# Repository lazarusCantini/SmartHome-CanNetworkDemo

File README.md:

# SmartHome-CanNetworkDemo
Dieses Repository beinhaltet alle Dateien die Nötig sind, um das CAN NetzwerkDemo-Board aufzubauen.
## Aufbau
### Schema

### Foto

### Pinbelegung für alle drei Arduinos gleich
CAN-BUS Modul | Arduino | ATMEGA328P
--------------|---------|-----------
INT (Invertiert)|2|PD2
SCK SPI CLK|13|PB5
SI MOSI|11|PB3
SO MISO|12|PB4
CS Chip Select|10|PB2
GND|GND|GND
VCC1 Versorgung|5V|\-
VCC Spg. Logikpegel|5V|\-

### Zuordnung ATMEGA328P Pins <-> Arduino
ATMEGA328P | Arduino
-----------|--------
PB0|8
PB1|9
PB2|10
PB3|11
PB4|12
PB5|13
PC0|A0
PC1|A1
PC2|A2
PC3|A3
PC4|A4
PC5|A5
PD0|0
PD1|1
PD2|2
PD3|3
PD4|4
PD5|5
PD6|6
PD7|7

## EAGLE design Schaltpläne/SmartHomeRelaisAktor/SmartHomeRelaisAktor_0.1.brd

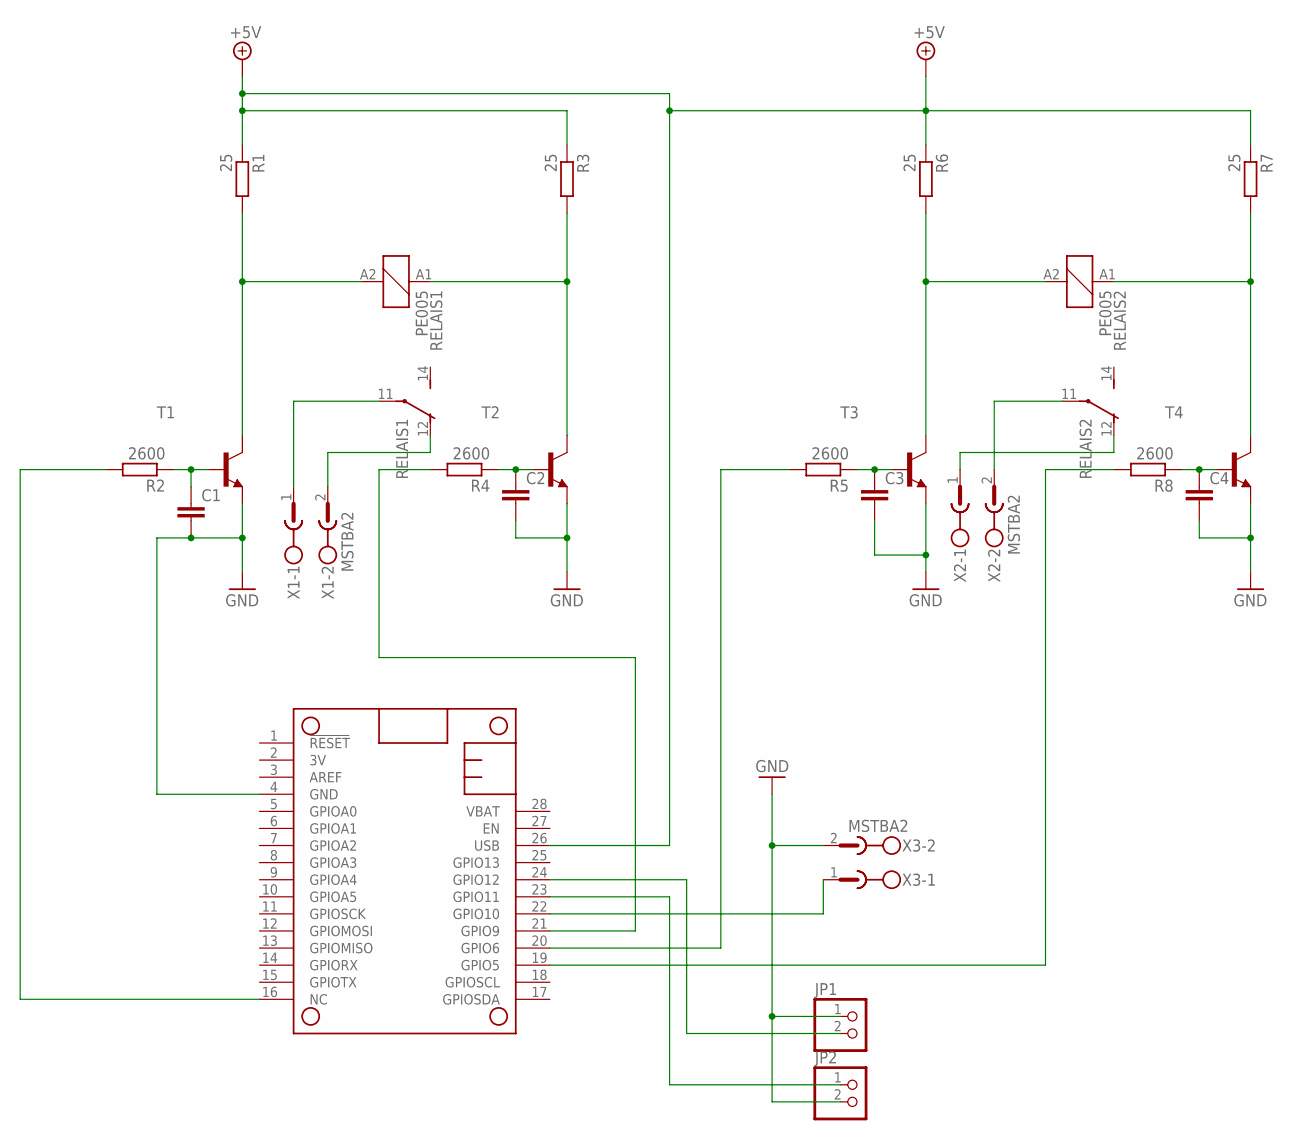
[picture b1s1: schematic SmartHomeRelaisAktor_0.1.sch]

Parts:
C1, C2, C3, C4: C-EUC0805; C0805
JP1, JP2: PINHD-1X2; 1X02
MS1: FEATHERWING
R1, R3, R6, R7: 25; R0805
R2, R4, R5, R8: 2600; R0805
RELAIS1, RELAIS2: PE005; PE
T1, T2, T3, T4: BC817-16-NPN-SOT23-BEC; SOT23-BEC
X1, X2, X3: MSTBA2

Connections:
GND: C1.2, C2.2, C3.2, C4.2, JP1.1, JP2.2, MS1.4 (GND), T1.E, T2.E, T3.E, T4.E, X3.2
unnamed: R1.2, RELAIS1.A2 (2), T1.C
unnamed: R3.2, RELAIS1.A1 (1), T2.C
unnamed: C2.1, R4.1, T2.B
unnamed: C3.1, R5.1, T3.B
unnamed: C1.1, R2.1, T1.B
unnamed: R6.2, RELAIS2.A2 (2), T3.C
unnamed: R7.2, RELAIS2.A1 (1), T4.C
unnamed: C4.1, R8.1, T4.B
unnamed: MS1.16 (NC), R2.2
unnamed: MS1.21 (GPIO9), R4.2
unnamed: MS1.20 (GPIO6), R5.2
unnamed: MS1.22 (GPIO10), X3.1
unnamed: RELAIS2.11, X2.2
unnamed: RELAIS1.12 (O), X1.2
unnamed: RELAIS1.11, X1.1
unnamed: MS1.19 (GPIO5), R8.2
unnamed: RELAIS2.12 (O), X2.1
unnamed: JP1.2, MS1.24 (GPIO12)
unnamed: JP2.1, MS1.23 (GPIO11)
USB: MS1.26 (USB), R1.1, R3.1, R6.1, R7.1

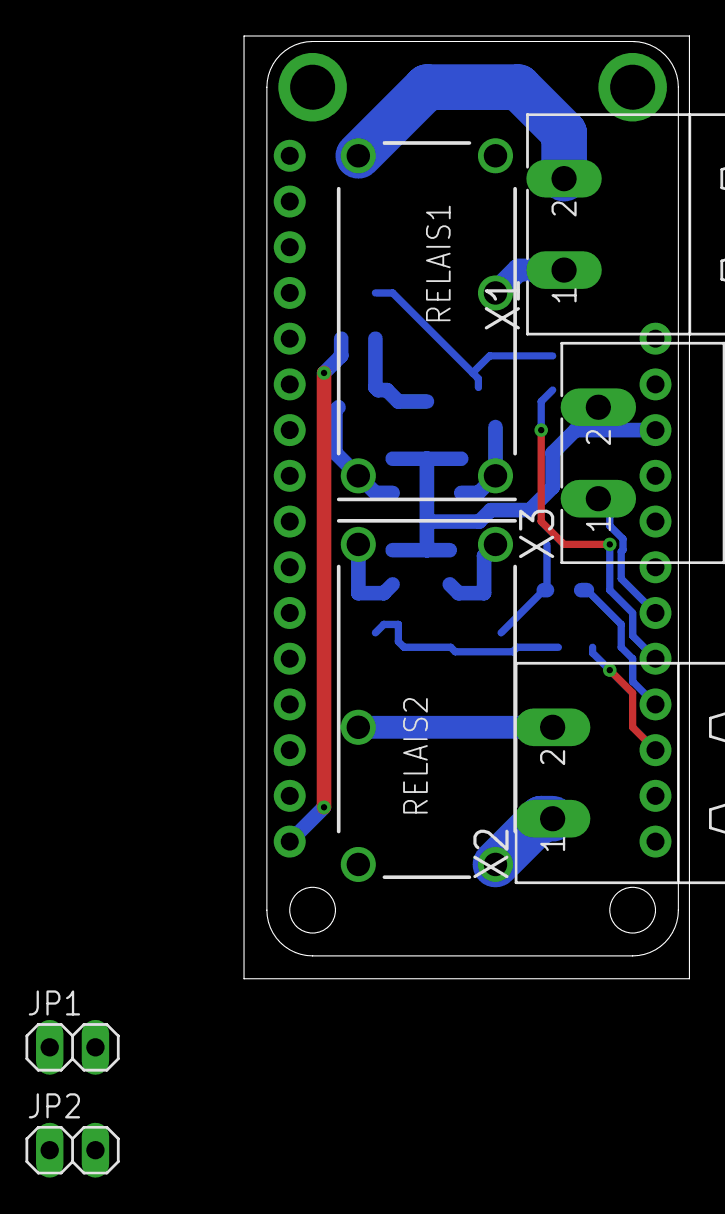
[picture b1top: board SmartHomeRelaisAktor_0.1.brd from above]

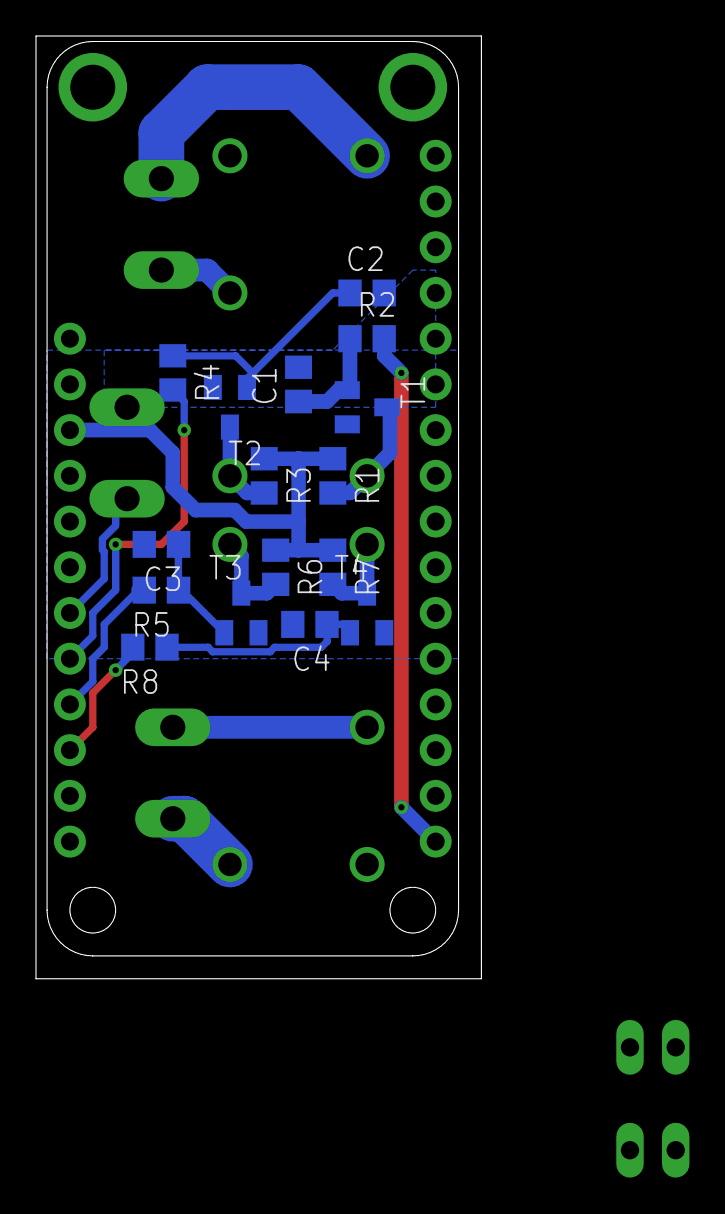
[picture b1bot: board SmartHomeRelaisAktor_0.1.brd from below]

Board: 2 copper layers, 24.7 x 52.4 mm, 24 parts (16 on the bottom side), 21 nets.

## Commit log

2019-03-28 Aufbau Schema gezeichnet
2019-03-29 Aufbau Schema Vervollständigt
2019-03-31 Quellcode für Node und HUB eingefügt
    Vom privaten Notebook aus dem AtmelStudio Ordner ins GitHub verschoben
2019-03-31 Ordner verschoben
2019-03-31 Kontrolliert: SetzeIDZusammen(uint8_t *CAN_Array)
    Die Funrktion wurde in C++ mit Codeblocks nachgeprüft und setzt das 8-Bit Array erwartungsmäß zusammen
2019-03-31 Arbeiten beendet
2019-04-02 Debugging ID Liste ausgabe wird noch korrigiert
2019-04-02 Batch Datei zum übertragen des Nodes vom Bürorechner aus erstellt
2019-04-03 Optimierung an Funktion void ID_Ausgeben(uint32_t ID) ausgeschaltet. Muss getestet werden, ob das eine Veränderung bringt
    __attribute__((optimize(0)))
2019-04-03 Create .gitignore
    Habe versucht alle Dateien auszunehmen, die sowieso bei jedem Kompiliervorgang neu erstellt werden, und unnötige "changed files" und History erzeugen
2019-04-03 void ID_Ausgeben(uint32_t ID) funktioniert endlich
2019-04-03 Versuche die automatisch generierten Dateien aus dem Projekt zu entfernen
2019-04-03 weitere automatisch generierten Dateien entfernt
2019-04-03 gitignore Test
2019-04-05 Pinout Arduino <-> ATMEGA328P hinzugefügt
2019-04-05 Pin Bibliothek hinzugefügt, und LED Pins definiert
2019-04-05 Revert "Pinout Arduino <-> ATMEGA328P hinzugefügt"
    This reverts commit 67fae2733ddc45ce7ad68df869293d14515be329.
2019-04-05 Revert "Revert "Pinout Arduino <-> ATMEGA328P hinzugefügt""
    This reverts commit 0b71fdb48e68ebb74e261073c404b3e81173cc3d.
2019-04-05 irgendwas ist schief gelaufen
2019-04-05 immer noch wiederherstellung
2019-04-05 imme rnoch
2019-04-05 Sensor Aktor Board wiederhergestellt
2019-04-05 Master funktioniert wieder
2019-04-05 Pin Bibliothek eingebunden und angefangen zu verwenden
2019-04-05 Angefangen mit dem remote schalten der LED
2019-04-08 Fast fertig mit Hardgecodetem Schalten einer LED. togglePin von ATMEGA328.cpp scheint nicht zu funktionieren
2019-04-08 Led wird per CAN Nachricht getoggelt
    Projekt To-Do Schalten eines Aktors über das CAN Netzwerk, getriggert Hardgecodet vom HUB ist abgeschlossen
2019-04-09 Beispiel CAN Arduino Script hinzugefügt
2019-04-10 Zweiten Node für Taster hinzugefügt
2019-04-10 Allen Text aus der Sketch.cpp von Node 1 in die Datei Sketch.cpp von Node2 kopiert
2019-04-10 Bild für Wiki eingefügt
2019-04-10 Bilder fürs Wiki hinzugefügt
2019-04-10 Bild für WIki hinzugefügt
2019-04-10 Bilder für Wiki hinzugefügt
2019-04-10 Diverseste Datein in das Projekt eingebunden, klappt aber immer noch nicht. Daher wird das Node2 projekt jetzt gelöscht, und danach nochmal ein AtmelStudio Projekt auf Grundlage eines Arduino Sketche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
    In dem Arduino Sketch befindet sich dann allerdings schon die Implementierung der CAN Bauteilbibliotheken.
2019-04-10 Programm fuer Node2 kompiliert endlich
2019-04-10 Node_02 fertig und bespielt
2019-04-10 Es funktioniert! Von Node2 aus wird ein Taster gedrückt, und an Node1 geht die LED an
2022-02-15 Feather Relais Wing Board
    Ein Feather Relais Wing Board mit Bistabilen Relais
2022-02-15 added secrets.py to gitignore
    In secrets.py sind die Zugangsdaten für den MQTT Server gespeichert. Daher darf die Datei nicht ins öffentliche repository fließen.
